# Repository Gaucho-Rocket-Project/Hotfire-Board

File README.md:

# DAQ Module — Sensor Data Logger

A compact sensor logging board for the **Gaucho Rocket Project (2026–27)**, designed by **Andrew Liu** at UC Santa Barbara. It replaces a perfboard-based logging system with a dedicated PCB for collecting rocket temperature and pressure data, with connections for future telemetry and sensor expansion.

## Key features

| Feature | Details |
| --- | --- |
| Microcontroller | STM32L496RET6 |
| Temperature | Four MAX31856 thermocouple interfaces |
| Pressure | Four 4–20 mA inputs with 130 Ω shunts and ADC protection |
| Storage | microSD via SDMMC |
| Connectivity | SPI expansion, two UART headers, USB-C, and SWD |
| Expansion | 4-to-16 decoder for SPI chip selection |
| Power | 9–12.6 V LiPo input; 15 V, 5 V, and 3.3 V rails; USB/battery power mux |
| Protection | Reverse-polarity protection, TVS/ESD protection, and a soft-start eFuse on the sensor supply |
| PCB | Four layers, approximately 78.68 × 71.02 mm |

## Design files

- [KiCad project](hotfire-board/Hotfire-Board.kicad_pro), [schematic](hotfire-board/Hotfire-Board.kicad_sch), and [PCB layout](hotfire-board/Hotfire-Board.kicad_pcb)
- [Custom symbols, footprints, and 3D models](hotfire-board/Project%20Libraries/)
- [Production exports](hotfire-board/production/): fabrication ZIP, BOM, and component placement files
- [Full design write-up](docs/Sensor_Data_Logger_Write_up.pdf): design rationale, power architecture, sensor interfaces, and PCB layout

Open the project in KiCad 10 or a compatible newer version. Keep the bundled libraries alongside the project so its relative library paths resolve.

## Firmware

The [firmware](firmware/) contains a Zephyr bring-up application for the STM32L496RE. It toggles **LED5 on PB1 every 500 ms** to check basic board operation. Temperature/pressure acquisition, microSD logging, and telemetry are not implemented yet.

The application uses the `nucleo_l496zg` build target with a custom board overlay. See the [firmware README](firmware/README.md) for environment setup, build commands, and flashing through an ST-LINK/SWD probe.

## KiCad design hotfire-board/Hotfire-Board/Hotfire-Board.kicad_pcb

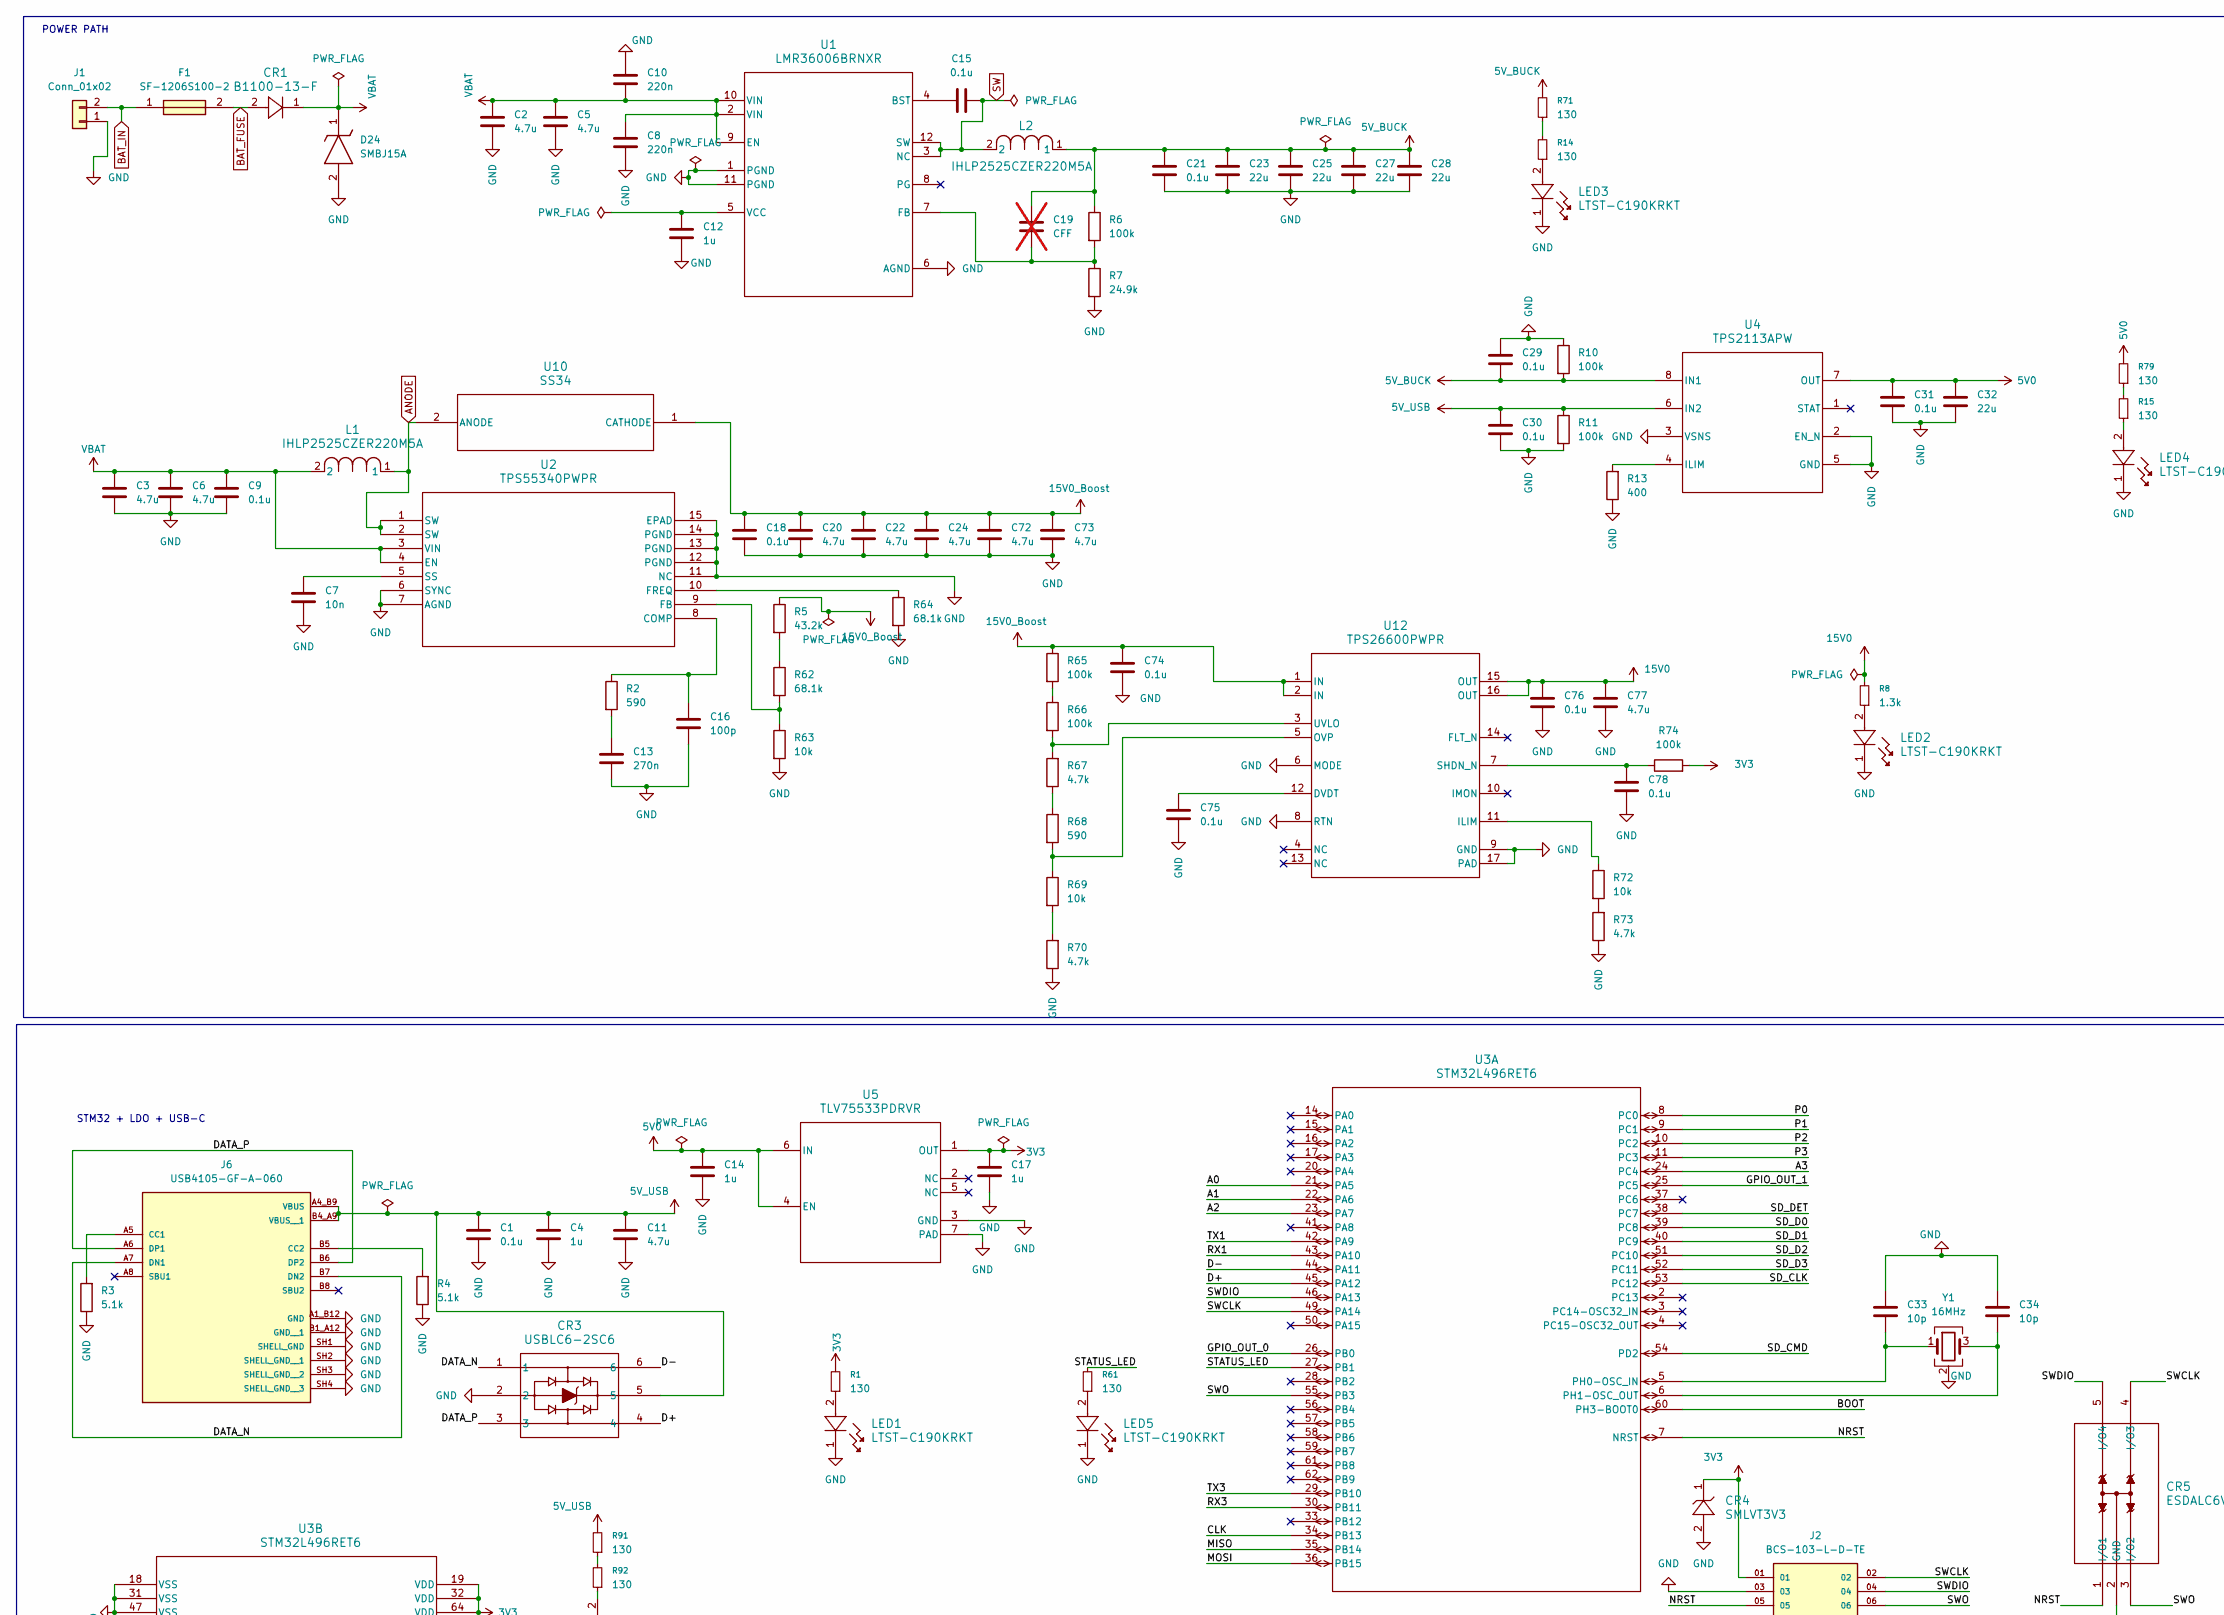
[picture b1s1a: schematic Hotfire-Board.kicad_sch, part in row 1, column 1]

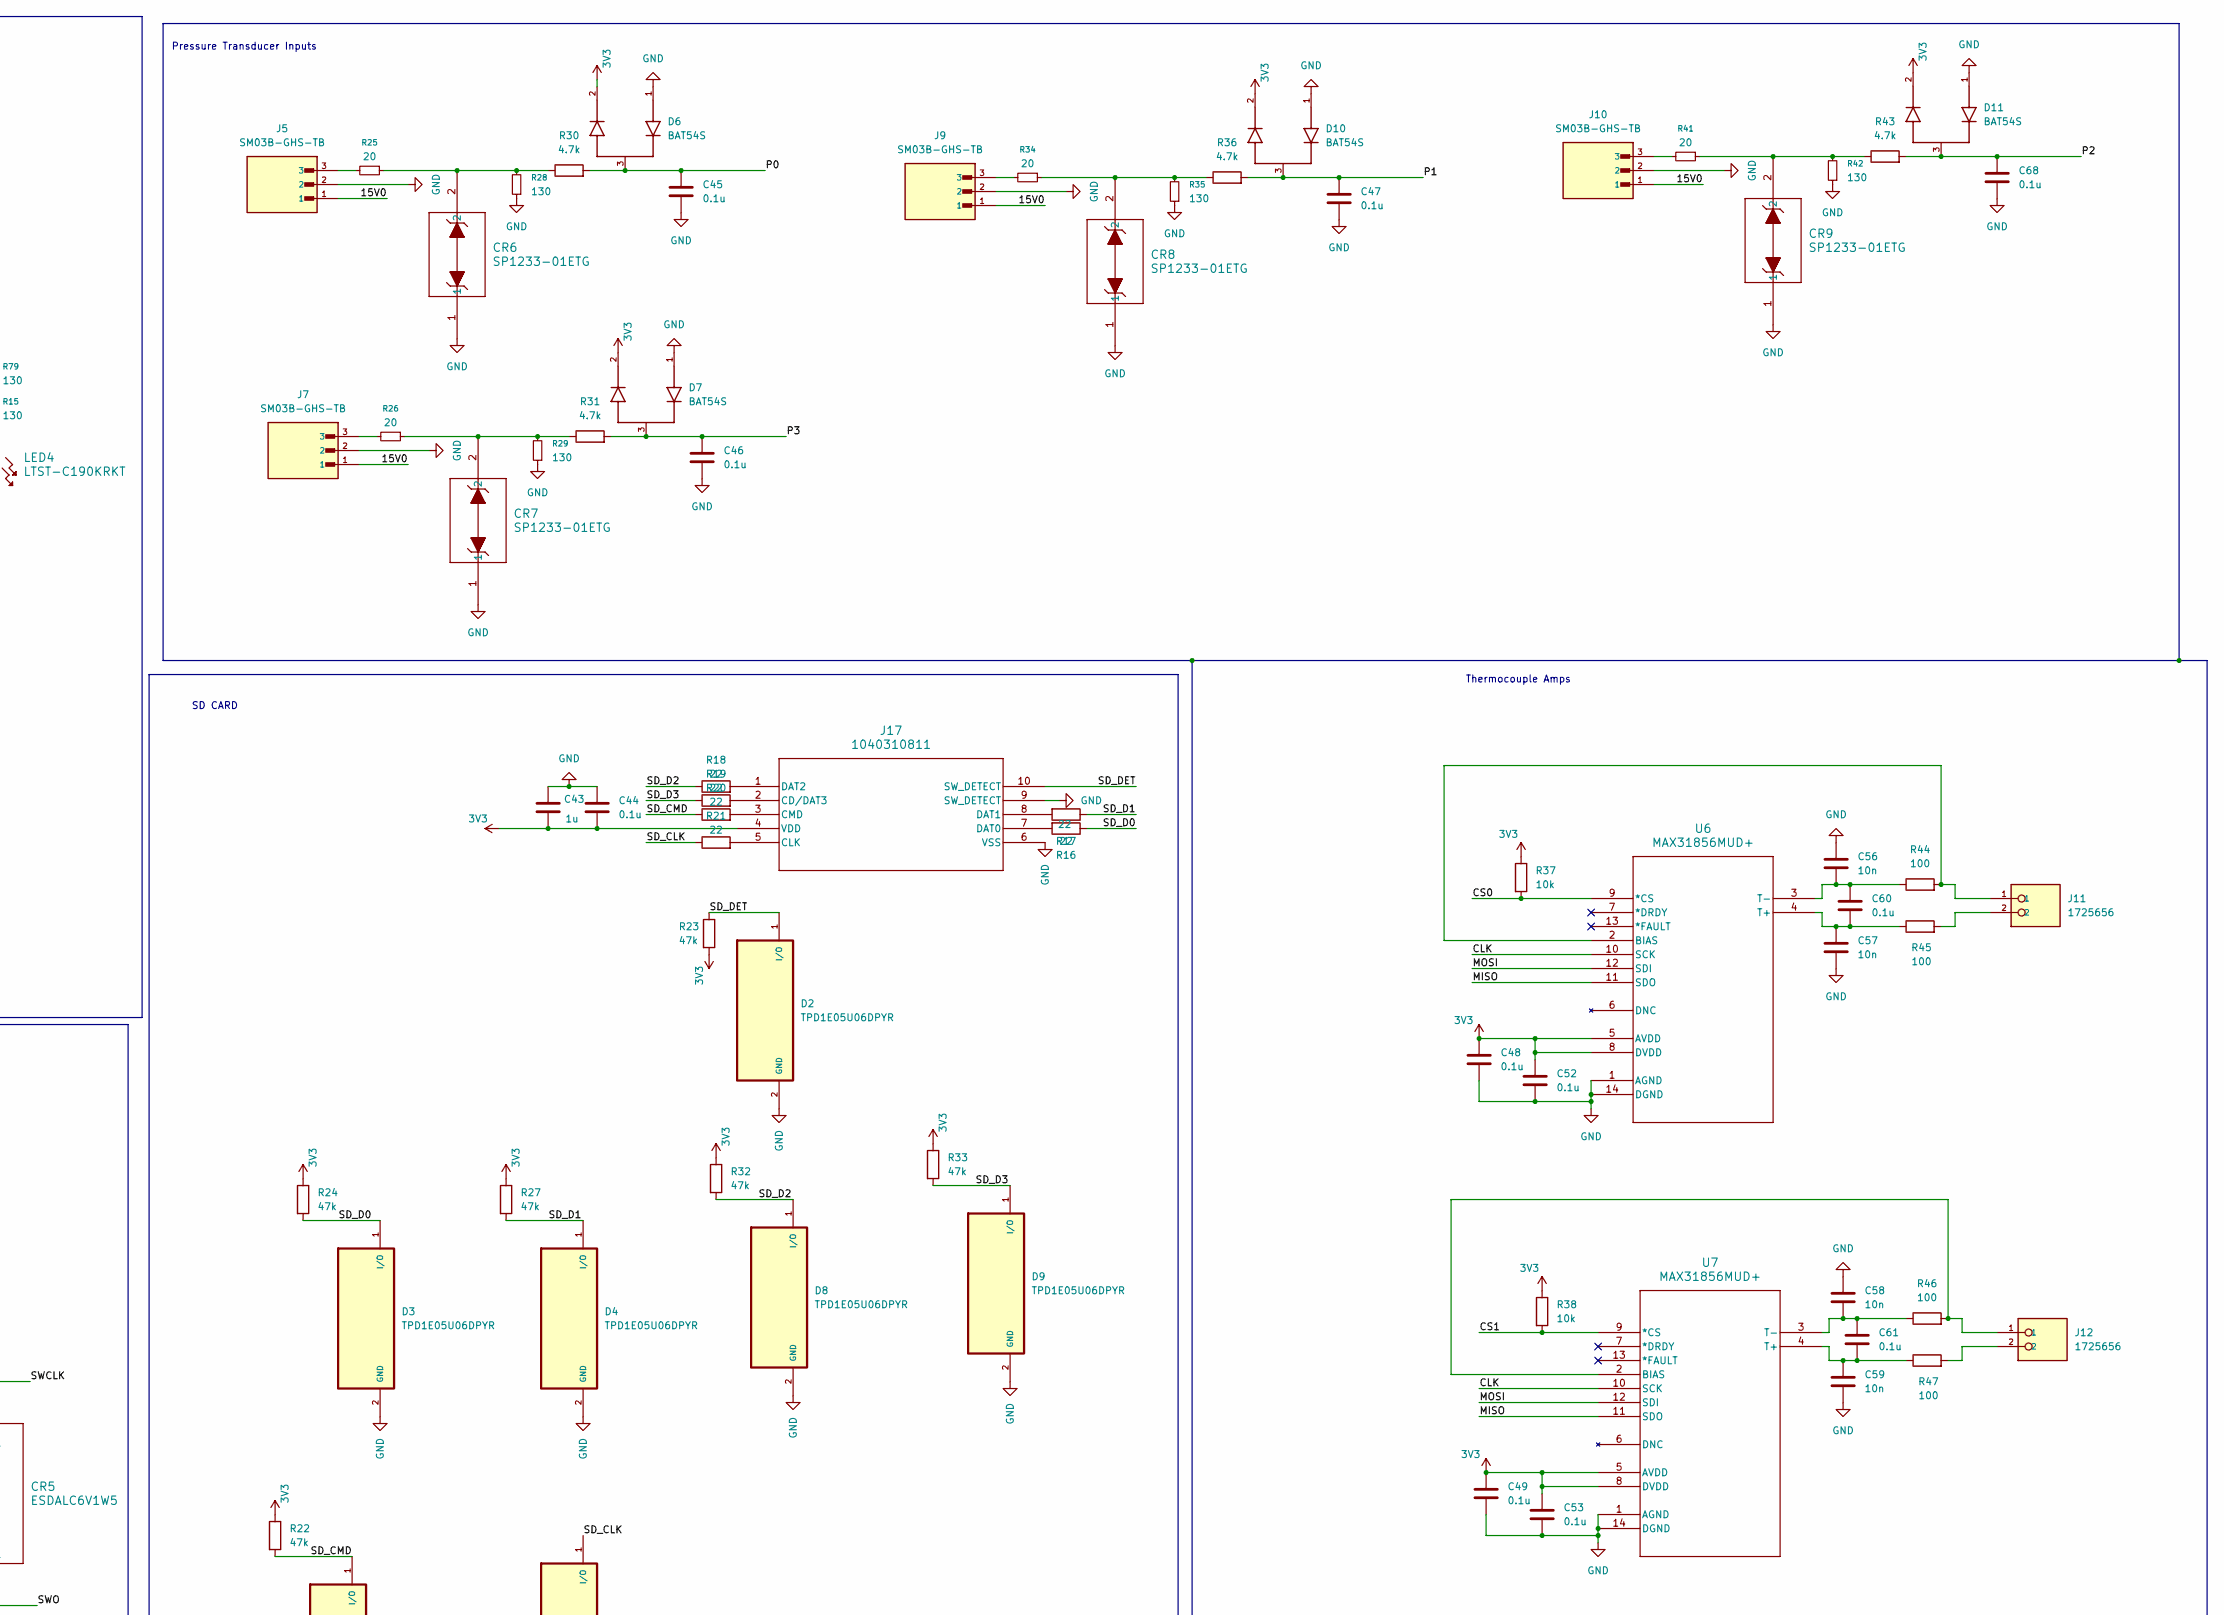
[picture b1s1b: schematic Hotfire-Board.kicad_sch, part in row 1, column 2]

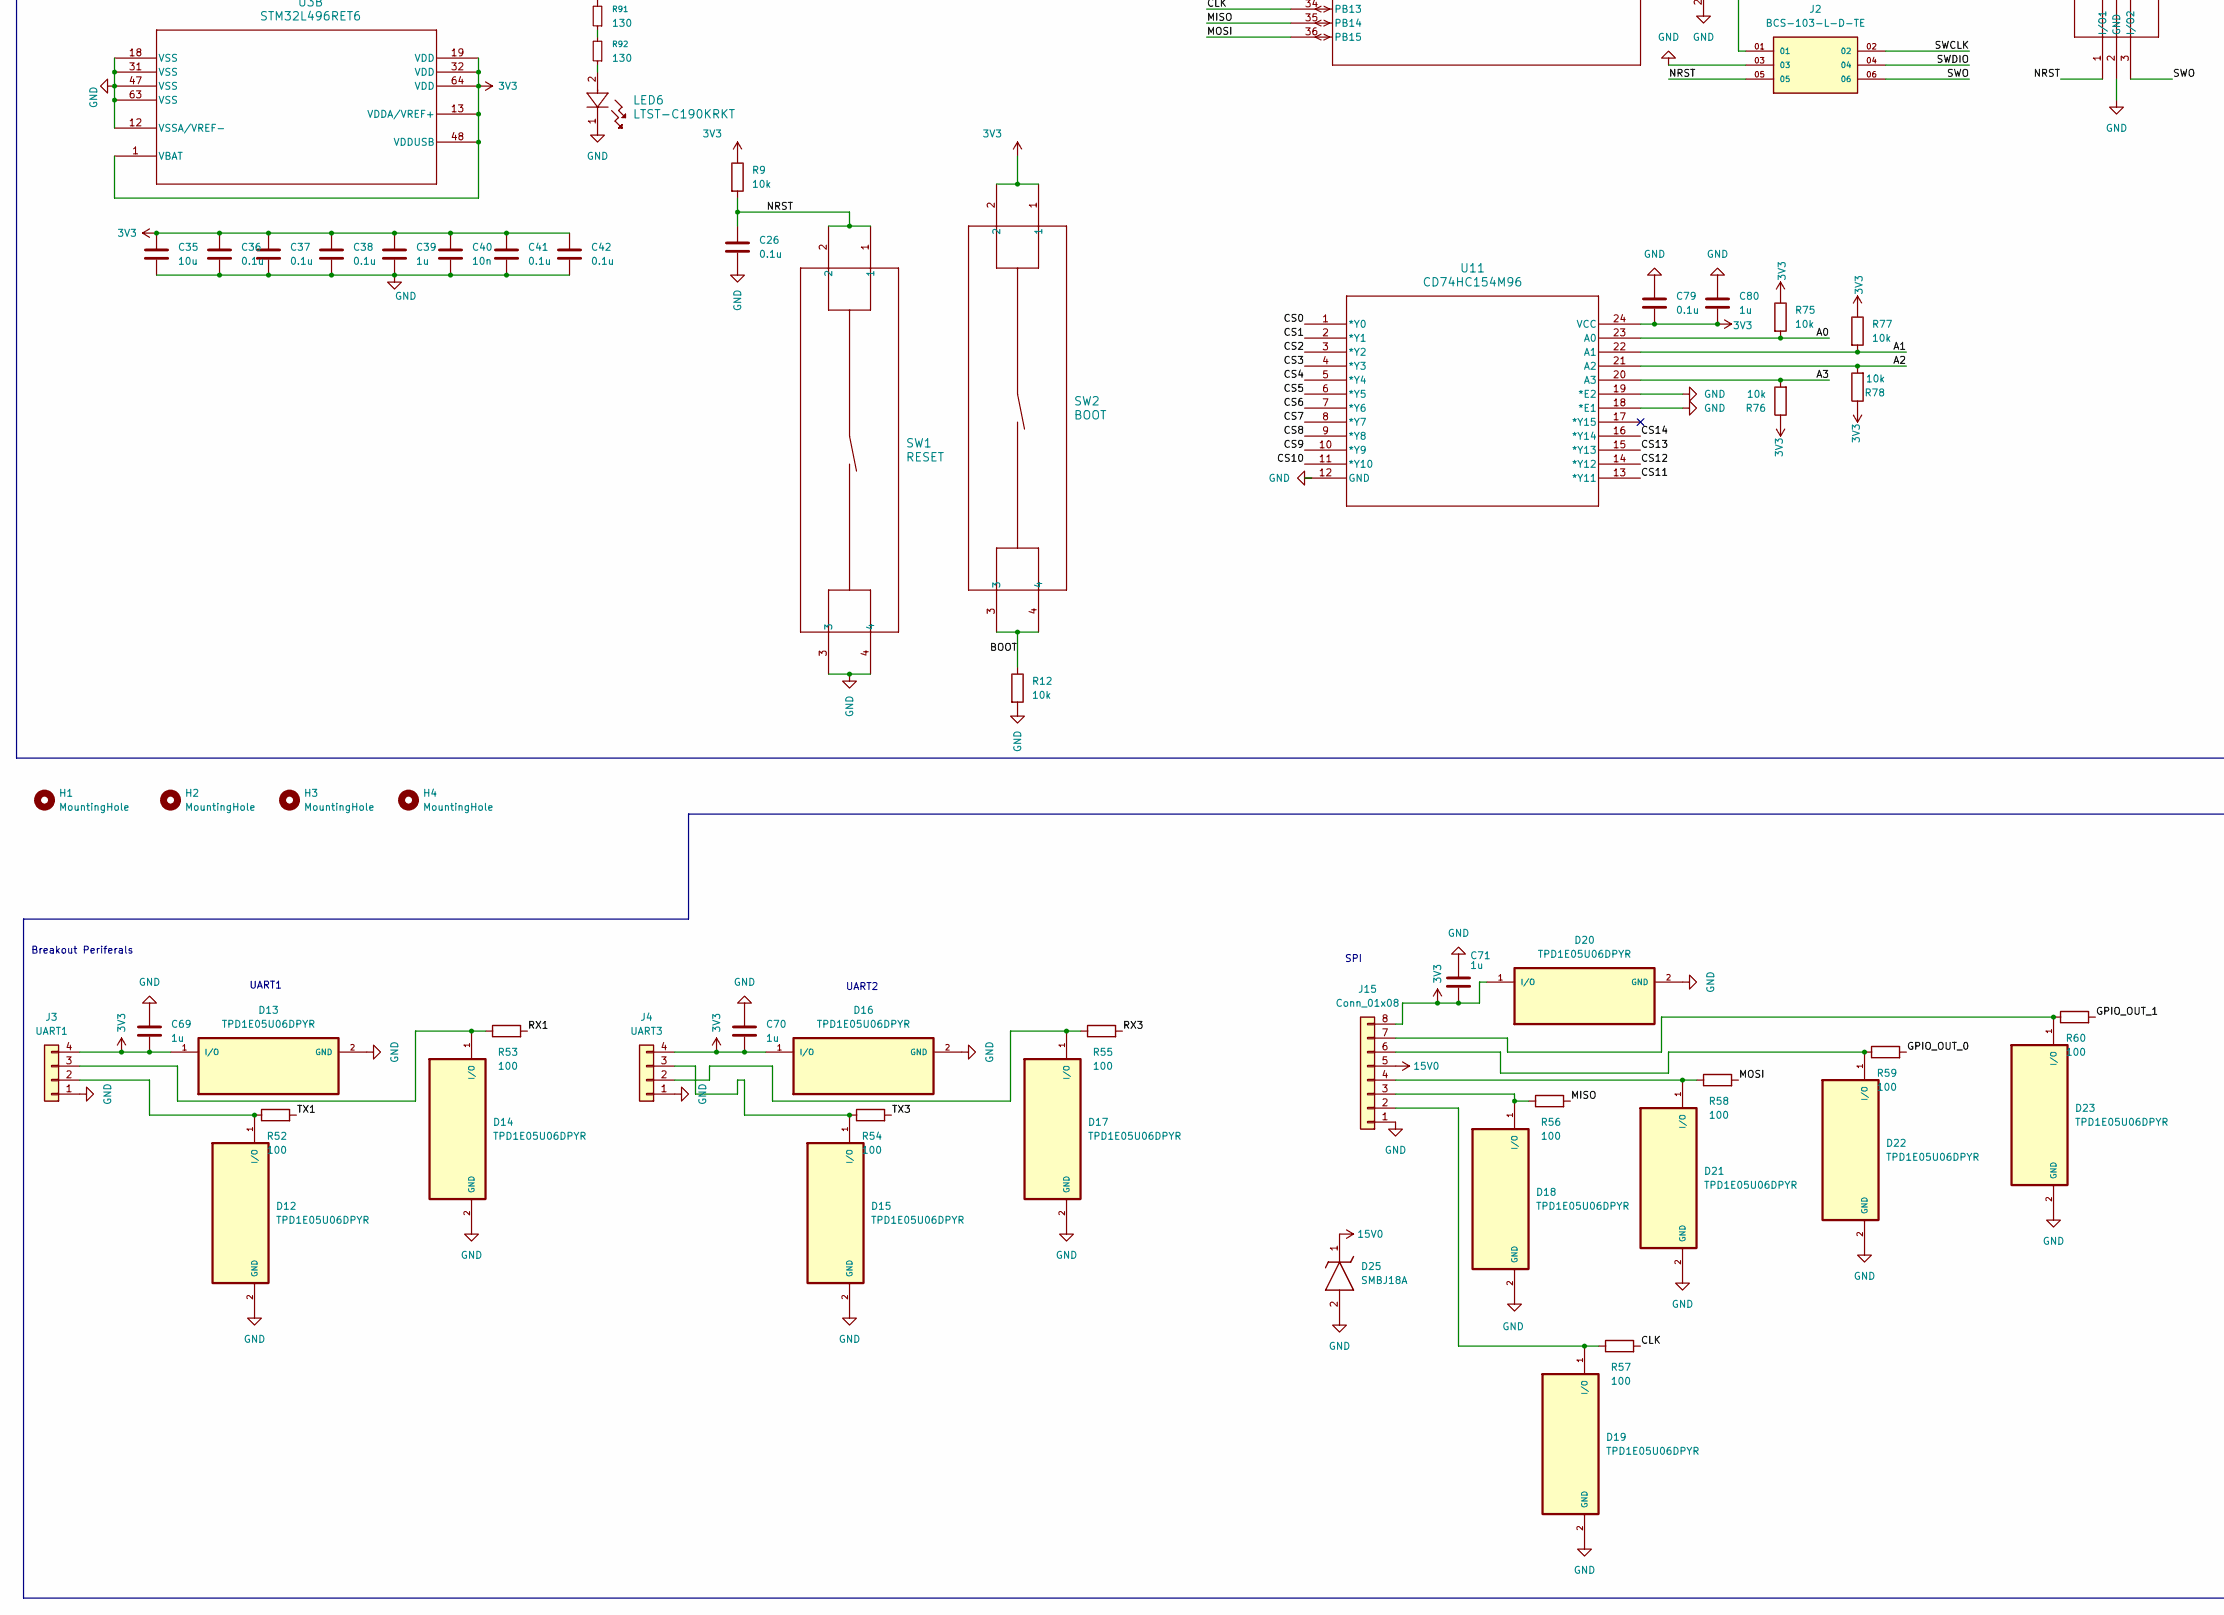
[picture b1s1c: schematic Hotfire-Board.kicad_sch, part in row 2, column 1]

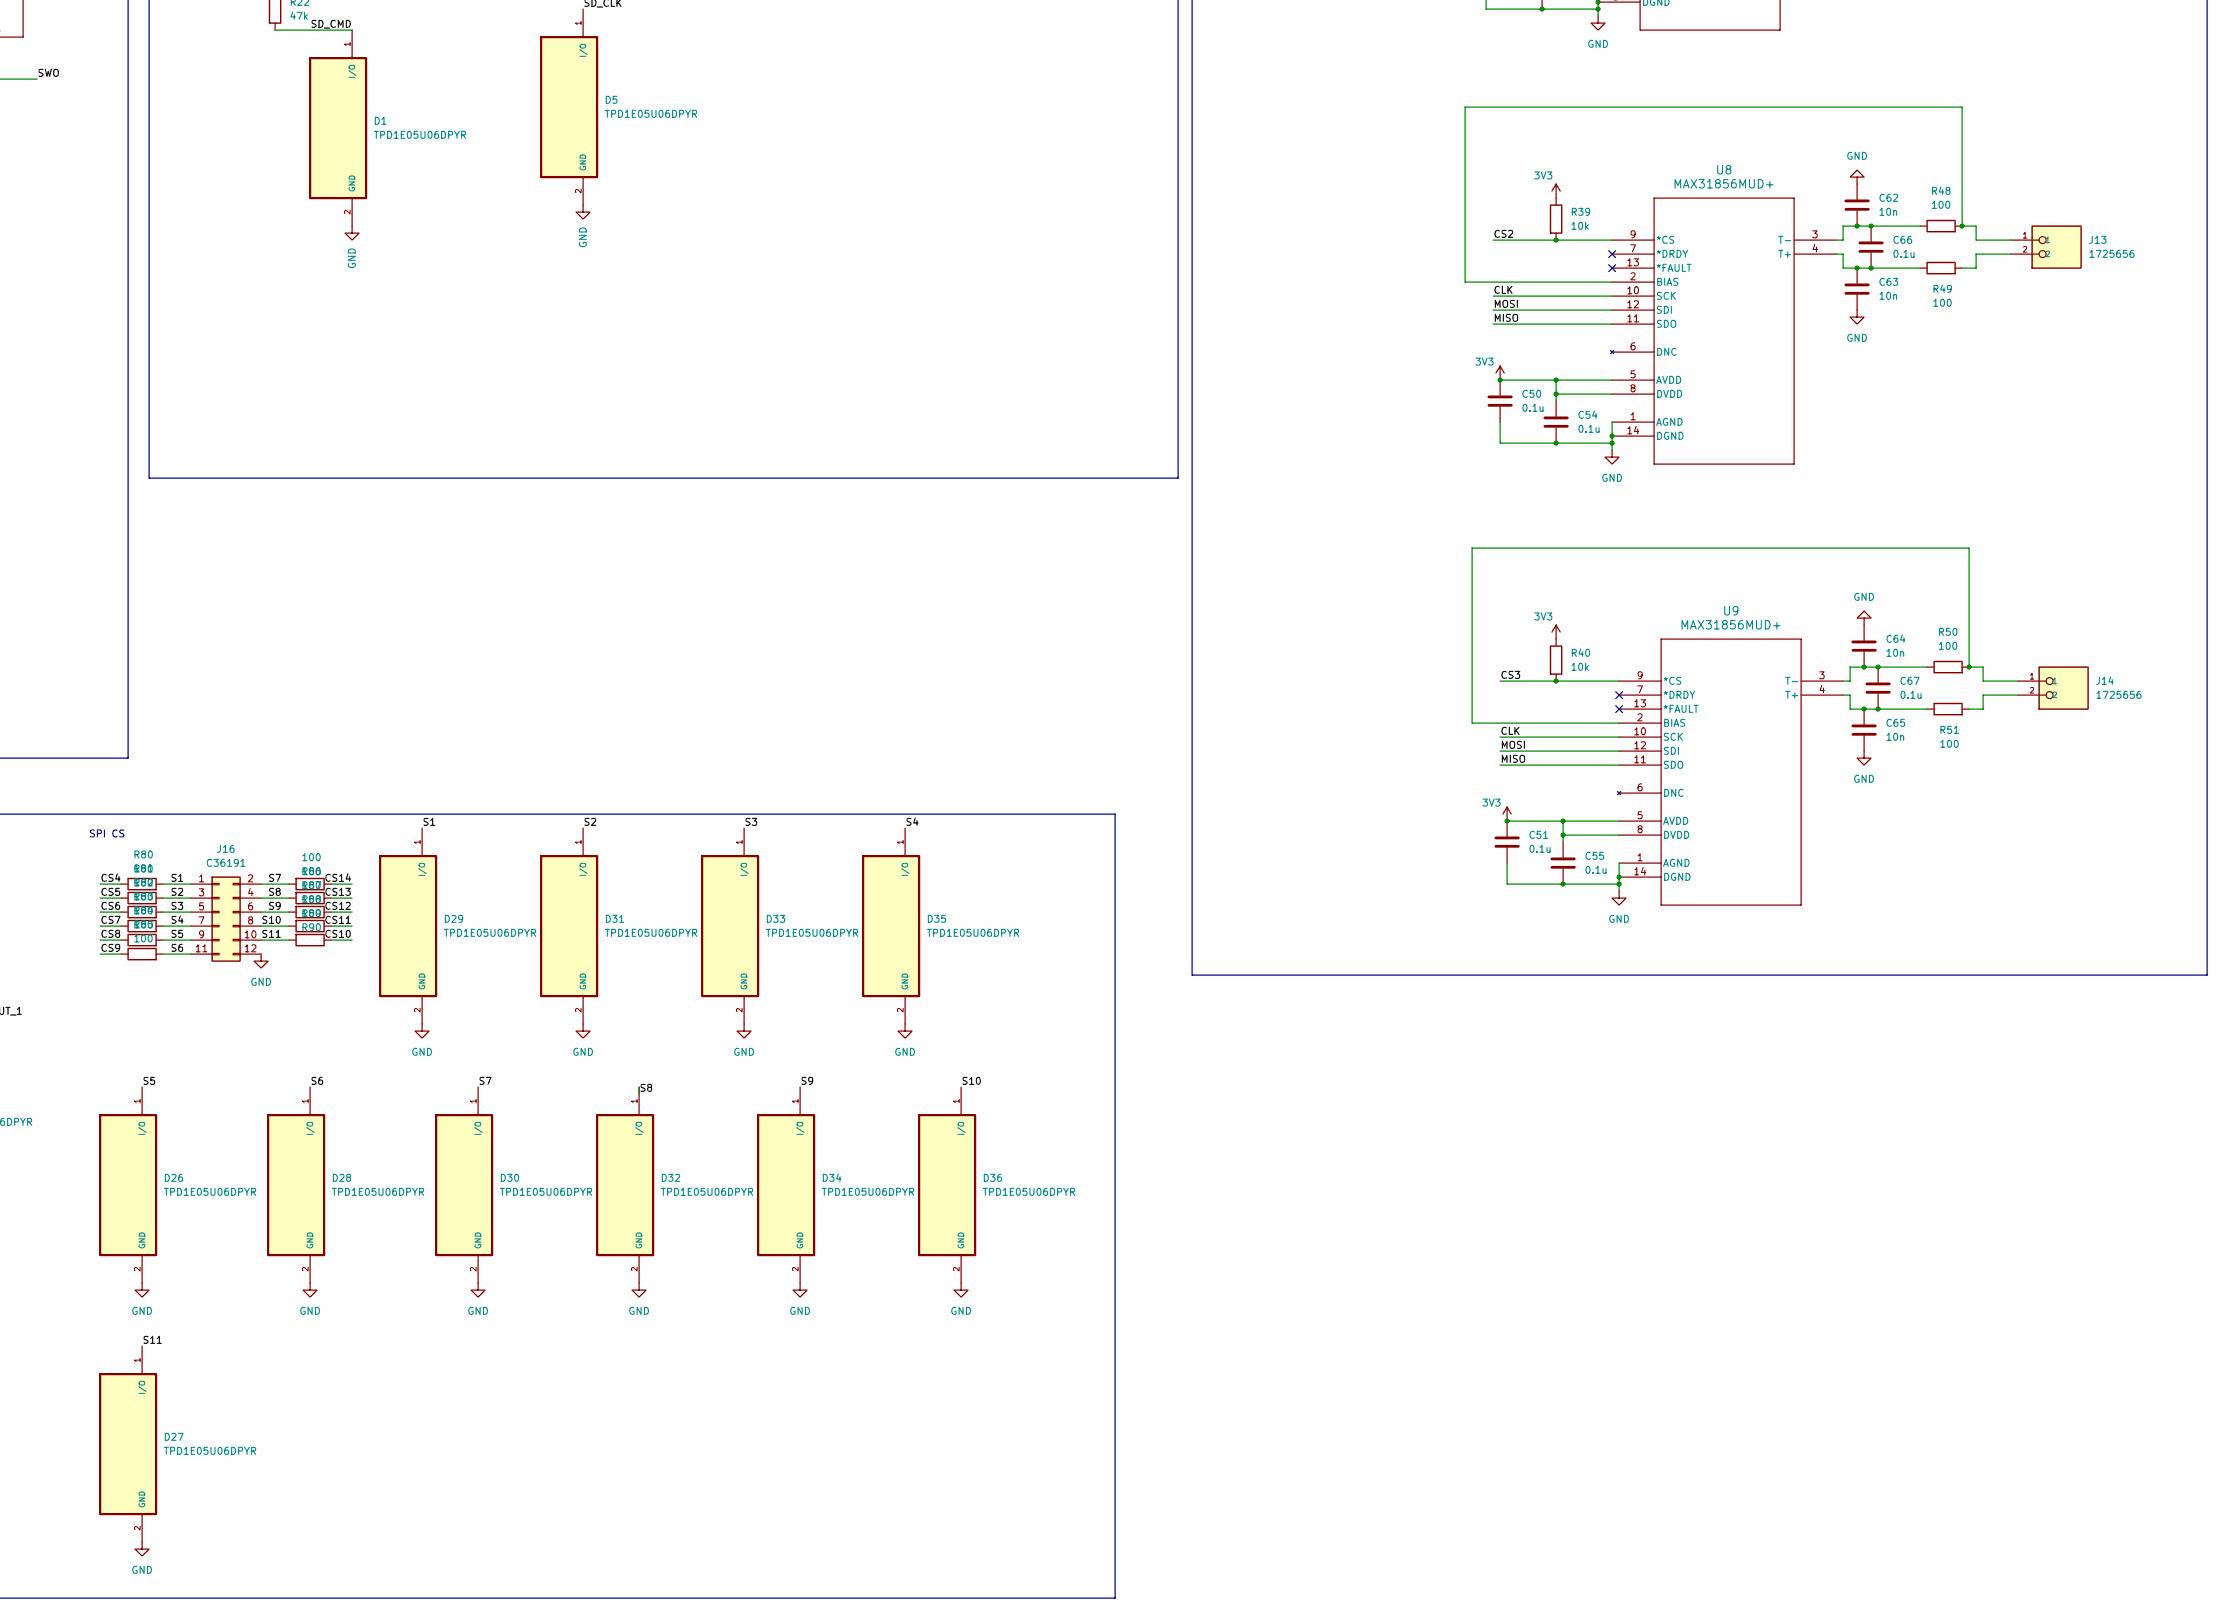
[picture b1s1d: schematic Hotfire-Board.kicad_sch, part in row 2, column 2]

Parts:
C1, C9, C15, C18, C21, C26, C29, C30, C31, C36, C37, C38, C41, C42, C44, C45, C46, C47, C48, C49, C50, C51, C52, C53, C54, C55, C60, C61, C66, C67, C68, C74, C75, C76, C78, C79: 0.1u; C_0402_1005Metric
C2, C3, C5, C6, C11, C20, C22, C24, C72, C73, C77: 4.7u; C_1206_3216Metric
C4, C12, C14, C17, C39, C43, C69, C70, C71, C80: 1u; C_0603_1608Metric
C7, C40, C56, C57, C58, C59, C62, C63, C64, C65: 10n; C_0402_1005Metric
C8, C10: 220n; C_0805_2012Metric
C13: 270n; C_0402_1005Metric
C16: 100p; C_0402_1005Metric
C19: CFF; C_0603_1608Metric; not fitted
C23, C25, C27, C28, C32: 22u; C_1206_3216Metric
C33, C34: 10p; C_0402_1005Metric
C35: 10u; C_1210_3225Metric
CR1: B1100-13-F; Shottkey_Rev_Bat
CR3: USBLC6-2SC6; ESDPROTECTION; MPN USBLC6-2SC6
CR4: SMLVT3V3; SWD_1_TVS
CR5: ESDALC6V1W5; SWD_4_TVS
CR6, CR7, CR8, CR9: SP1233-01ETG; TVS_Input
D1, D2, D3, D4, D5, D8, D9, D12, D13, D14, D15, D16, D17, D18, D19, D20, D21, D22, D23, D26, D27, D28, D29, D30, D31, D32, D33, D34, D35, D36: TPD1E05U06DPYR; SD_ESD
D6, D7, D10, D11: BAT54S; dual_shottkey; PARTREV 2.3; DigiKey_Part_Number 4786-BAT54SCT-ND
D24: SMBJ15A; 15V_TVS; Mouser Part Number 576-SMBJ15A
D25: SMBJ18A; 18V_TVS; Mouser Part Number 576-SMBJ18A
F1: SF-1206S100-2; fuse; Mouser Part Number 652-SF-1206S100-2
H1, H2, H3, H4: MountingHole; MountingHole_3.2mm_M3
J1: Conn_01x02; AMASS_XT60-M_1x02_P7.20mm_Vertical
J2: BCS-103-L-D-TE; 3x2_Header; PARTREV R
J3: UART1; PinSocket_1x04_P2.54mm_Vertical
J4: UART3; PinSocket_1x04_P2.54mm_Vertical
J5, J7, J9, J10: SM03B-GHS-TB; 3-pin-jst
J6: USB4105-GF-A-060; USB; PARTREV B3
J11, J12, J13, J14: 1725656; screw_terminal; PARTREV 03.03.2021
J15: Conn_01x08; PinSocket_1x08_P2.54mm_Vertical
J16: C36191; PinSocket_2x06_P2.54mm_Vertical
J17: 1040310811; newSD
L1, L2: IHLP2525CZER220M5A; 22uH
LED1, LED2, LED3, LED4, LED5, LED6: LTST-C190KRKT; red_LED
R1, R14, R15, R28, R29, R35, R42, R61, R71, R79, R91, R92: 130; R_0805_2012Metric
R2, R68: 590; R_0402_1005Metric
R3, R4: 5.1k; R_0603_1608Metric; MPN 0603WAF5101T5E
R5: 43.2k; R_0402_1005Metric
R6, R10, R11, R65, R66, R74: 100k; R_0402_1005Metric
R7: 24.9k; R_0402_1005Metric
R8: 1.3k; R_1206_3216Metric
R9, R12, R37, R38, R39, R40, R63, R69, R72, R75, R76, R77, R78: 10k; R_0402_1005Metric
R13: 400; R_0603_1608Metric; MPN PAT0603E4000BST1
R16, R17, R18, R19, R20, R21: 22; R_0402_1005Metric
R22, R23, R24, R27, R32, R33: 47k; R_0402_1005Metric
R25, R26, R34, R41: 20; R_1206_3216Metric
R30, R31, R36, R43, R67, R70, R73: 4.7k; R_0402_1005Metric
R44, R45, R46, R47, R48, R49, R50, R51, R52, R53, R54, R55, R56, R57, R58, R59, R60, R80, R81, R82, R83, R84, R85, R86, R87, R88, R89, R90: 100; R_0402_1005Metric
R62, R64: 68.1k; R_0402_1005Metric
SW1: RESET; SWITCH
SW2: BOOT; SWITCH
U1: LMR36006BRNXR; 3.3V_Buck
U2: TPS55340PWPR; 15V_Boost
U3: STM32L496RET6; STM32
U4: TPS2113APW; PowerMUXER.
U5: TLV75533PDRVR; newLDO
U6, U7, U8, U9: MAX31856MUD+; MAX
U10: SS34; Boost_Shottkey
U11: CD74HC154M96; 4-16-Multiplexer
U12: TPS26600PWPR; eFuse
Y1: 16MHz; Crystal_SMD_3225-4Pin_3.2x2.5mm

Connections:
3V3: C17.1, C35.1, C36.1, C37.1, C38.1, C39.1, C40.1, C41.1, C42.1, C43.1, C44.1, C48.1, C49.1, C50.1, C51.1, C52.1, C53.1, C54.1, C55.1, C69.2, C70.2, C71.2, C79.2, C80.2, CR4.1, D6.2, D7.2, D10.2, D11.2, D13.1 (I/O), D16.1 (I/O), D20.1 (I/O), J2.01, J3.4, J4.4, J15.8, J17.4 (VDD), R1.2, R9.1, R22.1, R23.2, R24.1, R27.1, R32.1, R33.1, R37.1, R38.1, R39.1, R40.1, R74.2, R75.1, R76.1, R77.1, R78.1, SW2.1, SW2.2, U3.1 (VBAT), U3.13 (VDDA/VREF+), U3.19 (VDD), U3.32 (VDD), U3.48 (VDDUSB), U3.64 (VDD), U5.1 (OUT), U6.5 (AVDD), U6.8 (DVDD), U7.5 (AVDD), U7.8 (DVDD), U8.5 (AVDD), U8.8 (DVDD), U9.5 (AVDD), U9.8 (DVDD), U11.24 (VCC)
5V0: C14.1, C31.1, C32.1, R79.2, U4.7 (OUT), U5.4 (EN), U5.6 (IN)
5V_BUCK: C19.1, C21.1, C23.1, C25.1, C27.1, C28.1, C29.2, L2.1, R6.1, R10.2, R71.2, U4.8 (IN1)
5V_USB: C1.2, C4.1, C11.1, C30.1, CR3.5, J6.A4_B9 (VBUS), J6.B4_A9 (VBUS__1), R11.1, R91.2, U4.6 (IN2)
15V0: C76.1, C77.1, D25.1 (K), J5.1, J7.1, J9.1, J10.1, J15.5, R8.2, U12.15 (OUT), U12.16 (OUT)
15V0_Boost: C18.1, C20.1, C22.1, C24.1, C72.1, C73.1, C74.1, R5.1, R65.1, U10.1 (CATHODE), U12.1 (IN), U12.2 (IN)
/A0: R75.2, U3.21 (PA5), U11.23 (A0)
/A1: R77.2, U3.22 (PA6), U11.22 (A1)
/A2: R78.2, U3.23 (PA7), U11.21 (A2)
/A3: R76.2, U3.24 (PC4), U11.20 (A3)
/BOOT: R12.1, SW2.3, SW2.4, U3.60 (PH3-BOOT0)
/CLK: R57.2, U3.34 (PB13), U6.10 (SCK), U7.10 (SCK), U8.10 (SCK), U9.10 (SCK)
/CS0: R37.2, U6.9 (*CS), U11.1 (*Y0)
/CS1: R38.2, U7.9 (*CS), U11.2 (*Y1)
/CS2: R39.2, U8.9 (*CS), U11.3 (*Y2)
/CS3: R40.2, U9.9 (*CS), U11.4 (*Y3)
/CS4: R80.1, U11.5 (*Y4)
/CS5: R81.1, U11.6 (*Y5)
/CS6: R82.1, U11.7 (*Y6)
/CS7: R83.1, U11.8 (*Y7)
/CS8: R84.1, U11.9 (*Y8)
/CS9: R85.1, U11.10 (*Y9)
/CS10: R90.1, U11.11 (*Y10)
/CS11: R89.1, U11.13 (*Y11)
/CS12: R88.1, U11.14 (*Y12)
/CS13: R87.1, U11.15 (*Y13)
/CS14: R86.1, U11.16 (*Y14)
/D+: CR3.4, U3.45 (PA12)
/D-: CR3.6, U3.44 (PA11)
/DATA_N: CR3.1, J6.A7 (DN1), J6.B7 (DN2)
/DATA_P: CR3.3, J6.A6 (DP1), J6.B6 (DP2)
/GPIO_OUT_0: R59.2, U3.26 (PB0)
/GPIO_OUT_1: R60.2, U3.25 (PC5)
/MISO: R56.2, U3.35 (PB14), U6.11 (SDO), U7.11 (SDO), U8.11 (SDO), U9.11 (SDO)
/MOSI: R58.2, U3.36 (PB15), U6.12 (SDI), U7.12 (SDI), U8.12 (SDI), U9.12 (SDI)
/NRST: C26.2, CR5.1 (I/O1), J2.05, R9.2, SW1.1, SW1.2, U3.7 (NRST)
/P0: C45.1, D6.3, R30.2, U3.8 (PC0)
/P1: C47.1, D10.3, R36.2, U3.9 (PC1)
/P2: C68.1, D11.3, R43.2, U3.10 (PC2)
/P3: C46.1, D7.3, R31.2, U3.11 (PC3)
/RX1: R53.2, U3.43 (PA10)
/RX3: R55.2, U3.30 (PB11)
/S1: D29.1 (I/O), J16.1, R80.2
/S2: D31.1 (I/O), J16.3, R81.2
/S3: D33.1 (I/O), J16.5, R82.2
/S4: D35.1 (I/O), J16.7, R83.2
/S5: D26.1 (I/O), J16.9, R84.2
/S6: D28.1 (I/O), J16.11, R85.2
/S7: D30.1 (I/O), J16.2, R86.2
/S8: D32.1 (I/O), J16.4, R87.2
/S9: D34.1 (I/O), J16.6, R88.2
/S10: D36.1 (I/O), J16.8, R89.2
/S11: D27.1 (I/O), J16.10, R90.2
/SD_CLK: D5.1 (I/O), R21.1, U3.53 (PC12)
/SD_CMD: D1.1 (I/O), R20.1, R22.2, U3.54 (PD2)
/SD_D0: D3.1 (I/O), R16.1, R24.2, U3.39 (PC8)
/SD_D1: D4.1 (I/O), R17.1, R27.2, U3.40 (PC9)
/SD_D2: D8.1 (I/O), R18.1, R32.2, U3.51 (PC10)
/SD_D3: D9.1 (I/O), R19.1, R33.2, U3.52 (PC11)
/SD_DET: D2.1 (I/O), J17.10 (SW_DETECT), R23.1, U3.38 (PC7)
/STATUS_LED: R61.2, U3.27 (PB1)
/SWCLK: CR5.4 (I/O3), J2.02, U3.49 (PA14)
/SWDIO: CR5.5 (I/O4), J2.04, U3.46 (PA13)
/SWO: CR5.3 (I/O2), J2.06, U3.55 (PB3)
/TX1: R52.2, U3.42 (PA9)
/TX3: R54.2, U3.29 (PB10)
ANODE: L1.1, U2.1 (SW), U2.2 (SW), U10.2 (ANODE)
BAT_FUSE: CR1.2, F1.2
BAT_IN: F1.1, J1.2
GND: C1.1, C2.2, C3.2, C4.2, C5.2, C6.2, C7.2, C8.1, C9.2, C10.1, C11.2, C12.2, C13.2, C14.2, C16.2, C17.2, C18.2, C20.2, C21.2, C22.2, C23.2, C24.2, C25.2, C26.1, C27.2, C28.2, C29.1, C30.2, C31.2, C32.2, C33.2, C34.2, C35.2, C36.2, C37.2, C38.2, C39.2, C40.2, C41.2, C42.2, C43.2, C44.2, C45.2, C46.2, C47.2, C48.2, C49.2, C50.2, C51.2, C52.2, C53.2, C54.2, C55.2, C56.1, C57.2, C58.1, C59.2, C62.1, C63.2, C64.1, C65.2, C68.2, C69.1, C70.1, C71.1, C72.2, C73.2, C74.2, C75.1, C76.2, C77.2, C78.2, C79.1, C80.1, CR3.2, CR4.2, CR5.2 (GND), CR6.1, CR7.1, CR8.1, CR9.1, D1.2 (GND), D2.2 (GND), D3.2 (GND), D4.2 (GND), D5.2 (GND), D6.1, D7.1, D8.2 (GND), D9.2 (GND), D10.1, D11.1, D12.2 (GND), D13.2 (GND), D14.2 (GND), D15.2 (GND), D16.2 (GND), D17.2 (GND), D18.2 (GND), D19.2 (GND), D20.2 (GND), D21.2 (GND), D22.2 (GND), D23.2 (GND), D24.2 (A), D25.2 (A), D26.2 (GND), D27.2 (GND), D28.2 (GND), D29.2 (GND), D30.2 (GND), D31.2 (GND), D32.2 (GND), D33.2 (GND), D34.2 (GND), D35.2 (GND), D36.2 (GND), J1.1, J2.03, J3.1, J4.1, J5.2, J6.A1_B12 (GND), J6.B1_A12 (GND__1), J6.SH1 (SHELL_GND), J6.SH2 (SHELL_GND__1), J6.SH3 (SHELL_GND__2), J6.SH4 (SHELL_GND__3), J7.2, J9.2, J10.2, J15.1, J16.12, J17.6 (VSS), J17.9 (SW_DETECT), LED1.1, LED2.1, LED3.1, LED4.1, LED5.1, LED6.1, R3.1, R4.1, R7.2, R10.1, R11.2, R12.2, R13.1, R28.1, R29.1, R35.1, R42.1, R63.2, R64.2, R70.1, R73.1, SW1.3, SW1.4, U1.1 (PGND), U1.6 (AGND), U1.11 (PGND), U2.6 (SYNC), U2.7 (AGND), U2.11 (NC), U2.12 (PGND), U2.13 (PGND), U2.14 (PGND), U2.15 (EPAD), U3.12 (VSSA/VREF-), U3.18 (VSS), U3.31 (VSS), U3.47 (VSS), U3.63 (VSS), U4.2 (EN_N), U4.3 (VSNS), U4.5 (GND), U5.3 (GND), U5.7 (PAD), U6.1 (AGND), U6.14 (DGND), U7.1 (AGND), U7.14 (DGND), U8.1 (AGND), U8.14 (DGND), U9.1 (AGND), U9.14 (DGND), U11.12 (GND), U11.18 (*E1), U11.19 (*E2), U12.6 (MODE), U12.8 (RTN), U12.9 (GND), U12.17 (PAD), Y1.2 (G), Y1.4 (G)
unnamed: C13.1, R2.2
unnamed: CR6.2, R25.1, R28.2, R30.1
unnamed: CR7.2, R26.1, R29.2, R31.1
unnamed: CR8.2, R34.1, R35.2, R36.1
unnamed: CR9.2, R41.1, R42.2, R43.1
unnamed: D12.1 (I/O), J3.2, R52.1
unnamed: D14.1 (I/O), J3.3, R53.1
unnamed: D15.1 (I/O), J4.3, R54.1
unnamed: D17.1 (I/O), J4.2, R55.1
unnamed: D18.1 (I/O), J15.3, R56.1
unnamed: D19.1 (I/O), J15.2, R57.1
unnamed: D21.1 (I/O), J15.4, R58.1
unnamed: D22.1 (I/O), J15.6, R59.1
unnamed: D23.1 (I/O), J15.7, R60.1
unnamed: J5.3, R25.2
unnamed: J6.A5 (CC1), R3.2
unnamed: J6.B5 (CC2), R4.2
unnamed: J7.3, R26.2
unnamed: J9.3, R34.2
unnamed: J10.3, R41.2
unnamed: J11.2, R45.2
unnamed: J12.2, R47.2
unnamed: J13.2, R49.2
unnamed: J14.2, R51.2
unnamed: J17.2 (CD/DAT3), R19.2
unnamed: J17.5 (CLK), R21.2
unnamed: J17.3 (CMD), R20.2
unnamed: J17.7 (DAT0), R16.2
unnamed: J17.8 (DAT1), R17.2
unnamed: J17.1 (DAT2), R18.2
unnamed: LED1.2, R1.1
unnamed: LED2.2, R8.1
unnamed: LED3.2, R14.1
unnamed: LED4.2, R15.1
unnamed: LED5.2, R61.1
unnamed: LED6.2, R92.1
unnamed: R5.2, R62.1
unnamed: R14.2, R71.1
unnamed: R15.2, R79.1
unnamed: R65.2, R66.1
unnamed: R67.1, R68.1
unnamed: R69.2, R70.2
unnamed: R72.2, R73.2
unnamed: R91.1, R92.2
unnamed: C15.1, U1.4 (BST)
unnamed: C19.2, R6.2, R7.1, U1.7 (FB)
unnamed: C12.1, U1.5 (VCC)
unnamed: C16.1, R2.1, U2.8 (COMP)
unnamed: R62.2, R63.1, U2.9 (FB)
unnamed: R64.1, U2.10 (FREQ)
unnamed: C7.1, U2.5 (SS)
unnamed: C33.1, U3.5 (PH0-OSC_IN), Y1.1
unnamed: C34.1, U3.6 (PH1-OSC_OUT), Y1.3
unnamed: R13.2, U4.4 (ILIM)
unnamed: J11.1, R44.2, U6.2 (BIAS)
unnamed: C57.1, C60.2, R45.1, U6.4 (T+)
unnamed: C56.2, C60.1, R44.1, U6.3 (T-)
unnamed: J12.1, R46.2, U7.2 (BIAS)
unnamed: C59.1, C61.2, R47.1, U7.4 (T+)
unnamed: C58.2, C61.1, R46.1, U7.3 (T-)
unnamed: J13.1, R48.2, U8.2 (BIAS)
unnamed: C63.1, C66.2, R49.1, U8.4 (T+)
unnamed: C62.2, C66.1, R48.1, U8.3 (T-)
unnamed: J14.1, R50.2, U9.2 (BIAS)
unnamed: C65.1, C67.2, R51.1, U9.4 (T+)
unnamed: C64.2, C67.1, R50.1, U9.3 (T-)
unnamed: C75.2, U12.12 (DVDT)
unnamed: R72.1, U12.11 (ILIM)
unnamed: R68.2, R69.1, U12.5 (OVP)
unnamed: C78.1, R74.1, U12.7 (SHDN_N)
unnamed: R66.2, R67.2, U12.3 (UVLO)
SW: C15.2, L2.2, U1.3 (NC), U1.12 (SW)
VBAT: C2.1, C3.1, C5.1, C6.1, C8.2, C9.1, C10.2, CR1.1, D24.1 (K), L1.2, U1.2 (VIN), U1.9 (EN), U1.10 (VIN), U2.3 (VIN), U2.4 (EN)

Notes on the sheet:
SPI CS
Thermocouple Amps
STM32 + LDO + USB-C
UART1
POWER PATH
UART2
SD CARD
SPI
Pressure Transducer Inputs
Breakout Periferals
